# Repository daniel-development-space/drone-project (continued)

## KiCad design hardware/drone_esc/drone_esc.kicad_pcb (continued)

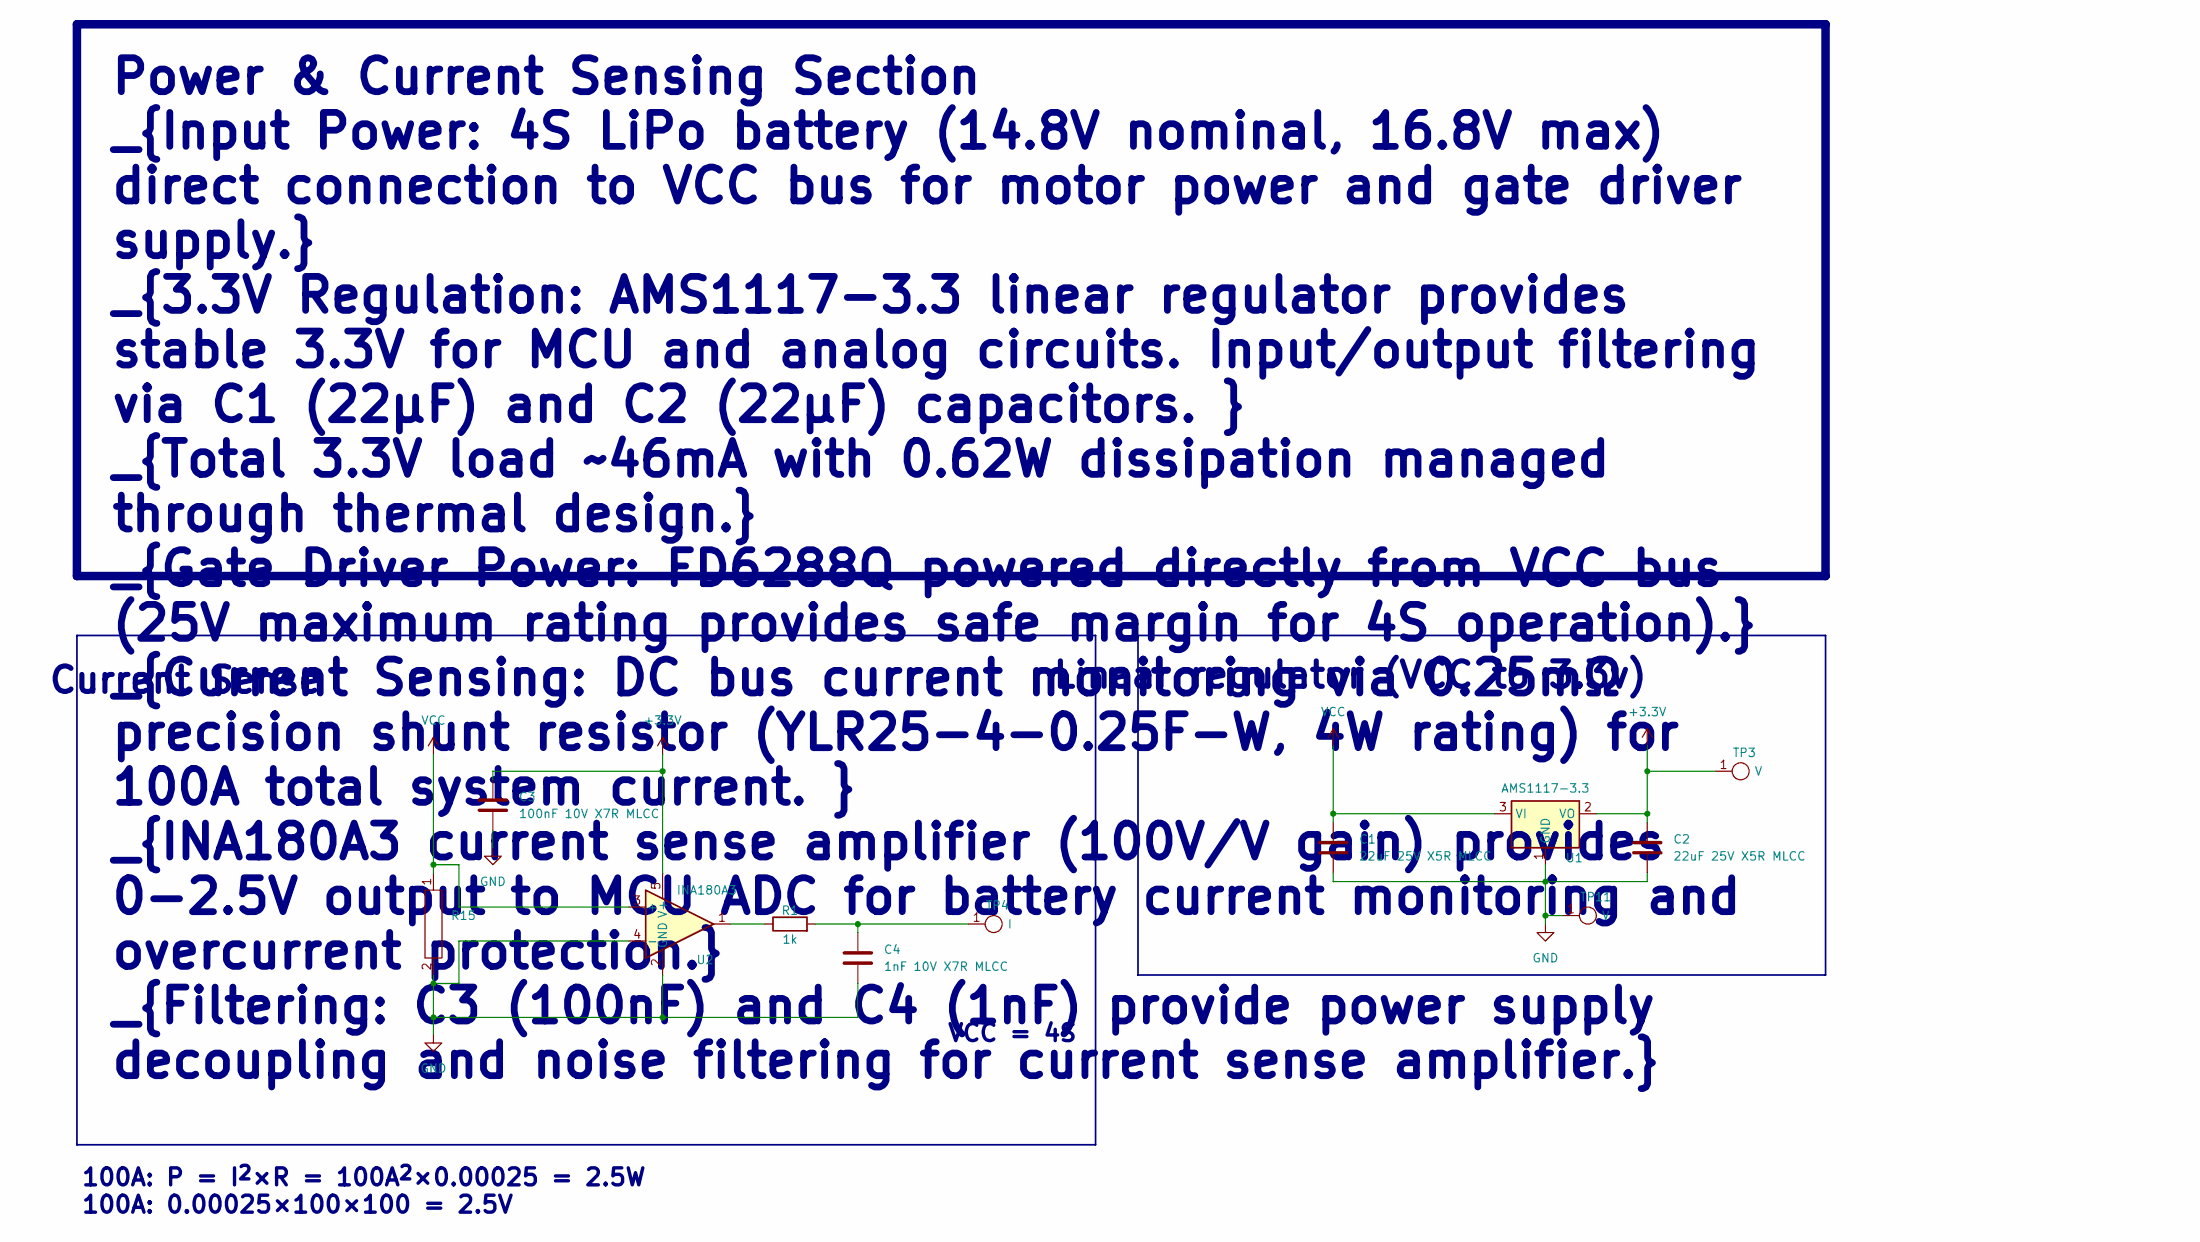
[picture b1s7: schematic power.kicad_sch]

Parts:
C1, C2: 22uF 25V X5R MLCC; C_0805_2012Metric; JLCPCB part C45783
C3: 100nF 10V X7R MLCC; C_0402_1005Metric; JLCPCB part C307331
C4: 1nF 10V X7R MLCC; C_0402_1005Metric; JLCPCB part C1523
R1: 1k; R_0402_1005Metric; JLCPCB part C11702
R15: YLR25-4-0.25F-W
TP3, TP11: V; Rectangle test point
TP4: I; Rectangle test point
U1: AMS1117-3.3; SOT-223-3_TabPin2; JLCPCB part C2688239
U2: INA180A3; SOT-23-5; JLCPCB part C122882

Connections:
+3.3V: C2.1, C3.1, TP3.1, U1.2 (VO), U2.5 (V+); also elsewhere on the board
GND: C1.2, C2.2, C3.2, C4.2, R15.2, TP11.1, U1.1 (GND), U2.2 (GND), U2.4 (-); also elsewhere on the board
unnamed: C4.1, R1.2, TP4.1
unnamed: R1.1, U2.1
VCC: C1.1, R15.1, U1.3 (VI), U2.3 (+); also elsewhere on the board

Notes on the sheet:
Linear regulator (VCC to 3.3v)
VCC = 4S
Current Sense
100A: P = I^{2}×R = 100A^{2}×0.00025 = 2.5W 100A: 0.00025×100×100 = 2.5V
Power & Current Sensing Section _{Input Power: 4S LiPo battery (14.8V nominal, 16.8V max) direct connection to VCC bus for motor power and gate driver supply.} _{3.3V Regulation: AMS1117-3.3 linear regulator provides stable 3.3V for MCU and analog circuits. Input/output filtering via C1 (22µF) and 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

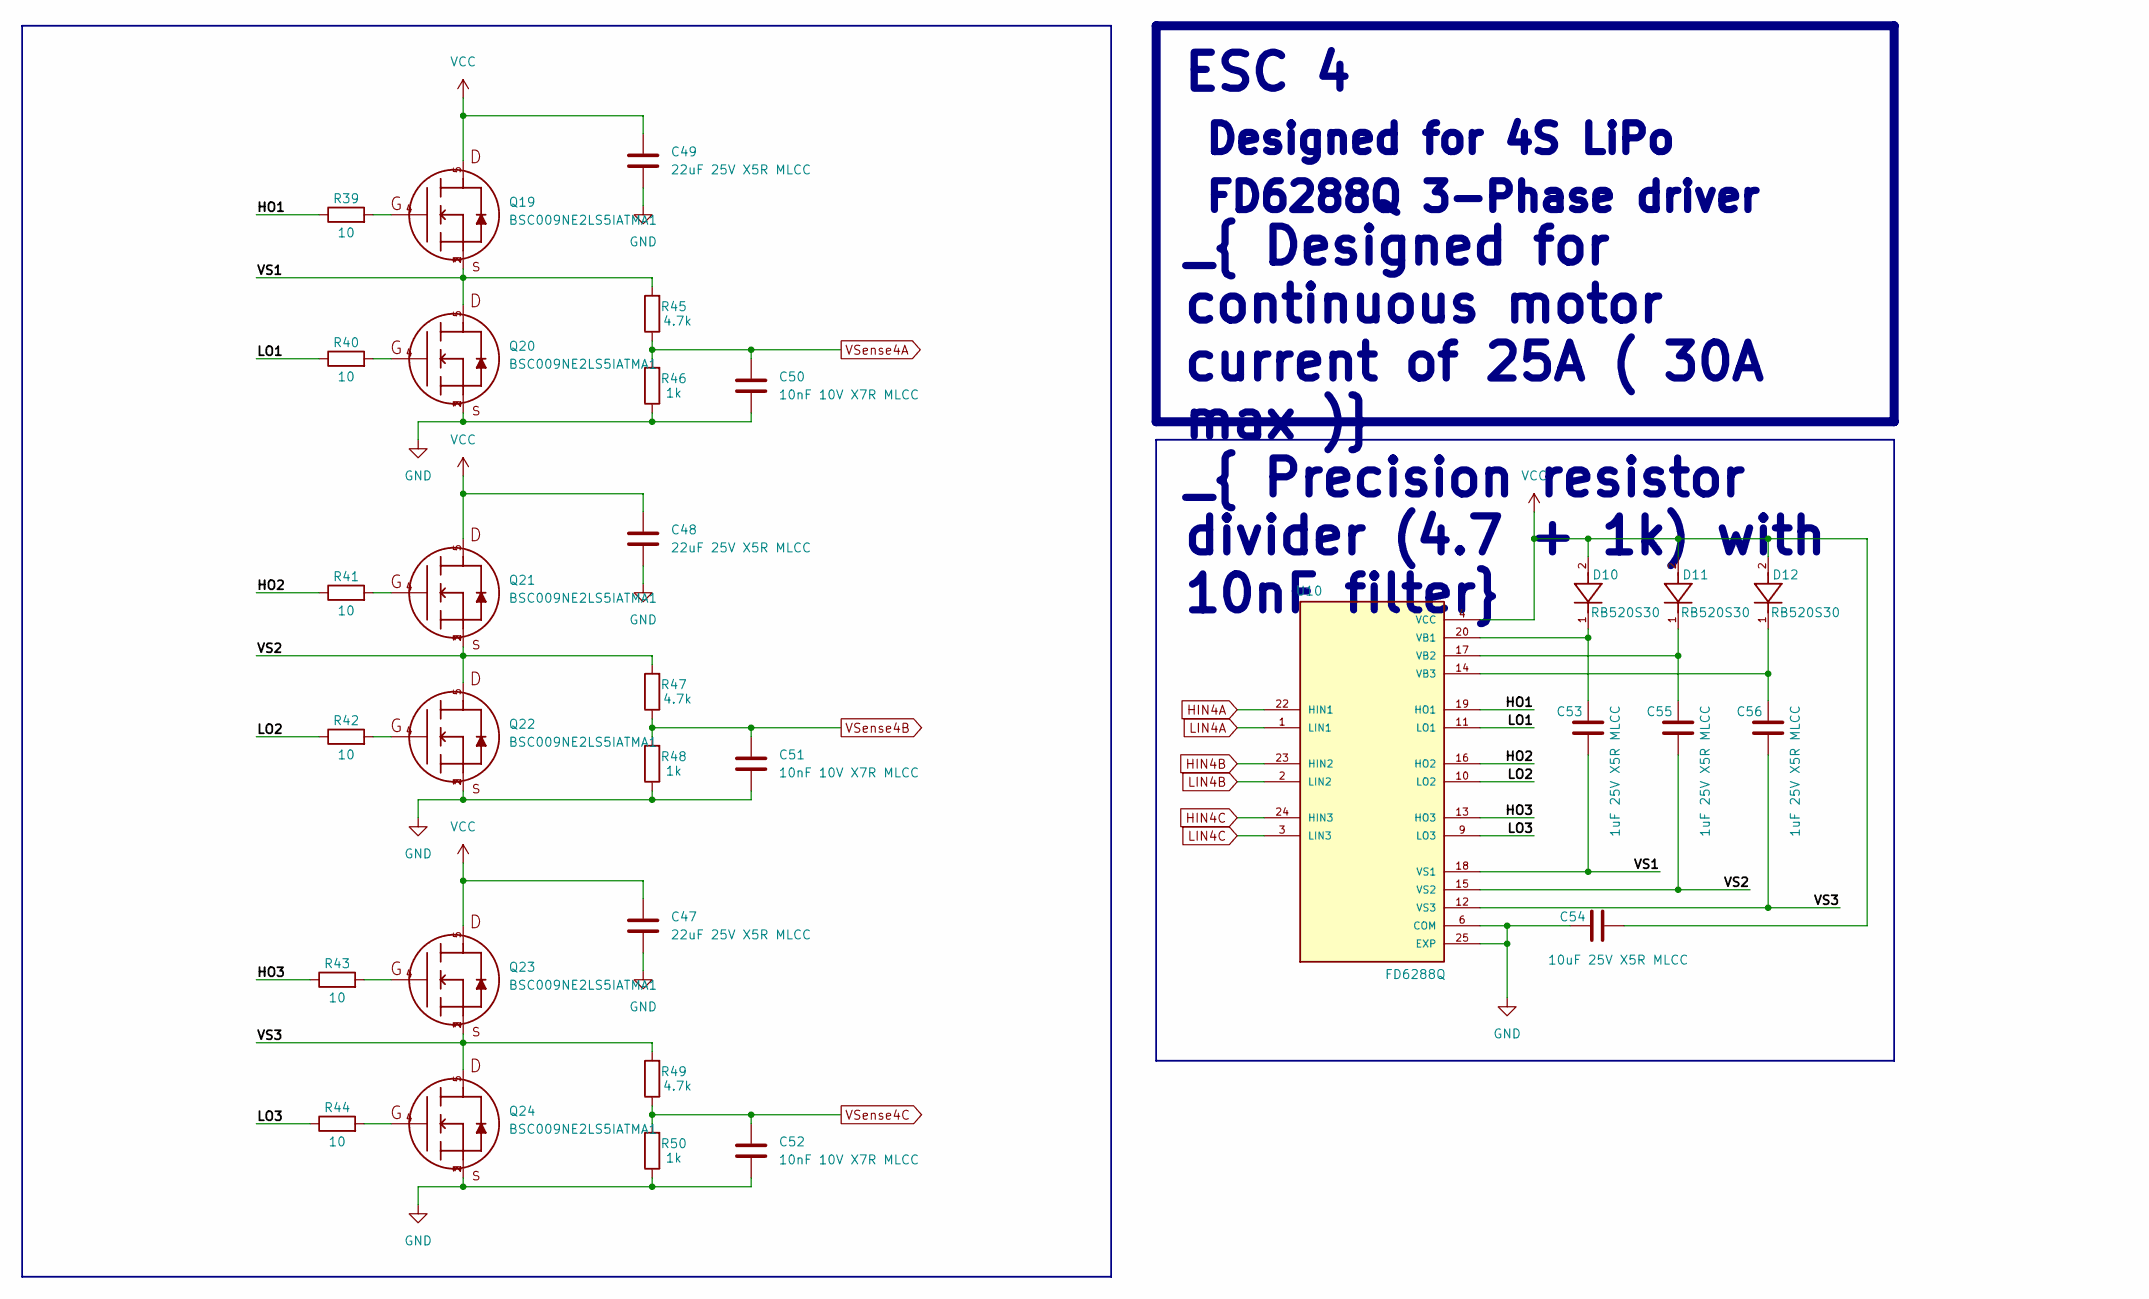
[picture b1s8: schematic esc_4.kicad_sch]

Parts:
C47, C48, C49: 22uF 25V X5R MLCC; C_0805_2012Metric; JLCPCB part C45783
C50, C51, C52: 10nF 10V X7R MLCC; C_0402_1005Metric; JLCPCB part C15195
C53, C55, C56: 1uF 25V X5R MLCC; C_0402_1005Metric; JLCPCB part C52923
C54: 10uF 25V X5R MLCC; C_0603_1608Metric; JLCPCB part C96446
D10, D11, D12: RB520S30; JLCPCB part C8522
Q19, Q20, Q21, Q22, Q23, Q24: BSC009NE2LS5IATMA1; BSC093N04LSGATMA1; JLCPCB part C122543
R39, R40, R41, R42, R43, R44: 10; R_0201_0603Metric; JLCPCB part C105889
R45, R47, R49: 4.7k; R_0402_1005Metric; JLCPCB part C25900
R46, R48, R50: 1k; R_0402_1005Metric; JLCPCB part C11702
U10: FD6288Q; JLCPCB part C328453

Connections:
/ESC4/HO1: R39.1, U10.19 (HO1)
/ESC4/HO2: R41.1, U10.16 (HO2)
/ESC4/HO3: R43.1, U10.13 (HO3)
/ESC4/LO1: R40.1, U10.11 (LO1)
/ESC4/LO2: R42.1, U10.10 (LO2)
/ESC4/LO3: R44.1, U10.9 (LO3)
/ESC4/VS1: C53.2, Q19.1, Q19.2, Q19.3, Q20.5, R45.2, U10.18 (VS1)
/ESC4/VS2: C55.2, Q21.1, Q21.2, Q21.3, Q22.5, R47.2, U10.15 (VS2)
/ESC4/VS3: C56.2, Q23.1, Q23.2, Q23.3, Q24.5, R49.2, U10.12 (VS3)
GND: C47.2, C48.2, C49.2, C50.2, C51.2, C52.2, C54.1, Q20.1, Q20.2, Q20.3, Q22.1, Q22.2, Q22.3, Q24.1, Q24.2, Q24.3, R46.1, R48.1, R50.1, U10.6 (COM), U10.25 (EXP); also elsewhere on the board
HIN4A: U10.22 (HIN1); also elsewhere on the board
HIN4B: U10.23 (HIN2); also elsewhere on the board
HIN4C: U10.24 (HIN3); also elsewhere on the board
LIN4A: U10.1 (LIN1); also elsewhere on the board
LIN4B: U10.2 (LIN2); also elsewhere on the board
LIN4C: U10.3 (LIN3); also elsewhere on the board
unnamed: Q19.4, R39.2
unnamed: Q20.4, R40.2
unnamed: Q21.4, R41.2
unnamed: Q22.4, R42.2
unnamed: Q23.4, R43.2
unnamed: Q24.4, R44.2
unnamed: C53.1, D10.1, U10.20 (VB1)
unnamed: C55.1, D11.1, U10.17 (VB2)
unnamed: C56.1, D12.1, U10.14 (VB3)
VCC: C47.1, C48.1, C49.1, C54.2, D10.2, D11.2, D12.2, Q19.5, Q21.5, Q23.5, U10.4 (VCC); also elsewhere on the board
VSense4A: C50.1, R45.1, R46.2; also elsewhere on the board
VSense4B: C51.1, R47.1, R48.2; also elsewhere on the board
VSense4C: C52.1, R49.1, R50.2; also elsewhere on the board

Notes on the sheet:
ESC 4 _{ Designed for 4S LiPo} _{ FD6288Q 3-Phase driver} _{ Designed for continuous motor current of 25A ( 30A max )} _{ Precision resistor divider (4.7 + 1k) with 10nF filter}

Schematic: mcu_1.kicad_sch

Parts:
C5: 4.7uF 10V X5R MLCC; C_0402_1005Metric; JLCPCB part C23733
C6: 100nF 10V X7R MLCC; C_0402_1005Metric; JLCPCB part C307331
C7: 100nF 16V X7R MLCC; C_0402_1005Metric; JLCPCB part C307331
TP1: 1.27 test pad
TP2: DShot; Rectangle test point
U3: STM32G071GBUxN; QFN-28_4x4mm_P0.5mm

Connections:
+3.3V: C5.1, C6.1, TP1.1 (V), U3.3 (VDD); also elsewhere on the board
/MCU1/SWCLK: TP1.3 (SWCLK), U3.21 (PA14)
/MCU1/SWDIO: TP1.2 (SWDIO), U3.20 (PA13)
GND: C5.2, C6.2, C7.1, TP1.4 (GND), U3.4 (VSS); also elsewhere on the board
HIN1A: U3.19 (PA10/PA12); also elsewhere on the board
HIN1B: U3.18 (PA9/PA11); also elsewhere on the board
HIN1C: U3.16 (PA8); also elsewhere on the board
LIN1A: U3.15 (PB15); also elsewhere on the board
LIN1B: U3.14 (PB0); also elsewhere on the board
LIN1C: U3.13 (PA7); also elsewhere on the board
unnamed: TP2.1, U3.28 (PB8)
unnamed: C7.2, U3.5 (PF2)
VSense1A: U3.6 (PA0); also elsewhere on the board
VSense1B: U3.7 (PA1); also elsewhere on the board
VSense1C: U3.8 (PA2); also elsewhere on the board

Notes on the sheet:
STM32G071GBU6
SWD Debugging
Microcontroller 1 _{Processor: 32-bit ARM Cortex-M0+ running at 64MHz for real-time 3-phase motor control and sensorless commutation algorithms.} _{Power: 3.3V regulated supply with C5 (1µF) and C6 (100nF) decoupling capacitors for stable operation.} _{Reset: PF2-NRST with C7 (100nF) filtering. Int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

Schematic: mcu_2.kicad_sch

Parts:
C18: 4.7uF 10V X5R MLCC; C_0402_1005Metric; JLCPCB part C23733
C19: 100nF 16V X7R MLCC; C_0402_1005Metric; JLCPCB part C307331
C20: 100nF 10V X7R MLCC; C_0402_1005Metric; JLCPCB part C307331
TP5: DShot; Rectangle test point
TP6: 1.27 test pad
U5: STM32G071GBU6; QFN-28_4x4mm_P0.5mm; JLCPCB part C529347

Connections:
+3.3V: C18.1, C20.1, TP6.1 (V), U5.3 (VDD); also elsewhere on the board
/MCU2/SWCLK: TP6.3 (SWCLK), U5.21 (PA14)
/MCU2/SWDIO: TP6.2 (SWDIO), U5.20 (PA13)
GND: C18.2, C19.1, C20.2, TP6.4 (GND), U5.4 (VSS); also elsewhere on the board
HIN2A: U5.19 (PA10/PA12); also elsewhere on the board
HIN2B: U5.18 (PA9/PA11); also elsewhere on the board
HIN2C: U5.16 (PA8); also elsewhere on the board
LIN2A: U5.15 (PB15); also elsewhere on the board
LIN2B: U5.14 (PB0); also elsewhere on the board
LIN2C: U5.13 (PA7); also elsewhere on the board
unnamed: TP5.1, U5.28 (PB8)
unnamed: C19.2, U5.5 (PF2)
VSense2A: U5.6 (PA0); also elsewhere on the board
VSense2B: U5.7 (PA1); also elsewhere on the board
VSense2C: U5.8 (PA2); also elsewhere on the board

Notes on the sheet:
SWD Debugging
STM32G071GBU6
Microcontroller 2 _{Processor: 32-bit ARM Cortex-M0+ running at 64MHz for real-time 3-phase motor control and sensorless commutation algorithms.} _{Power: 3.3V regulated supply with C5 (1µF) and C6 (100nF) decoupling capacitors for stable operation.} _{Reset: PF2-NRST with C7 (100nF) filtering. Int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

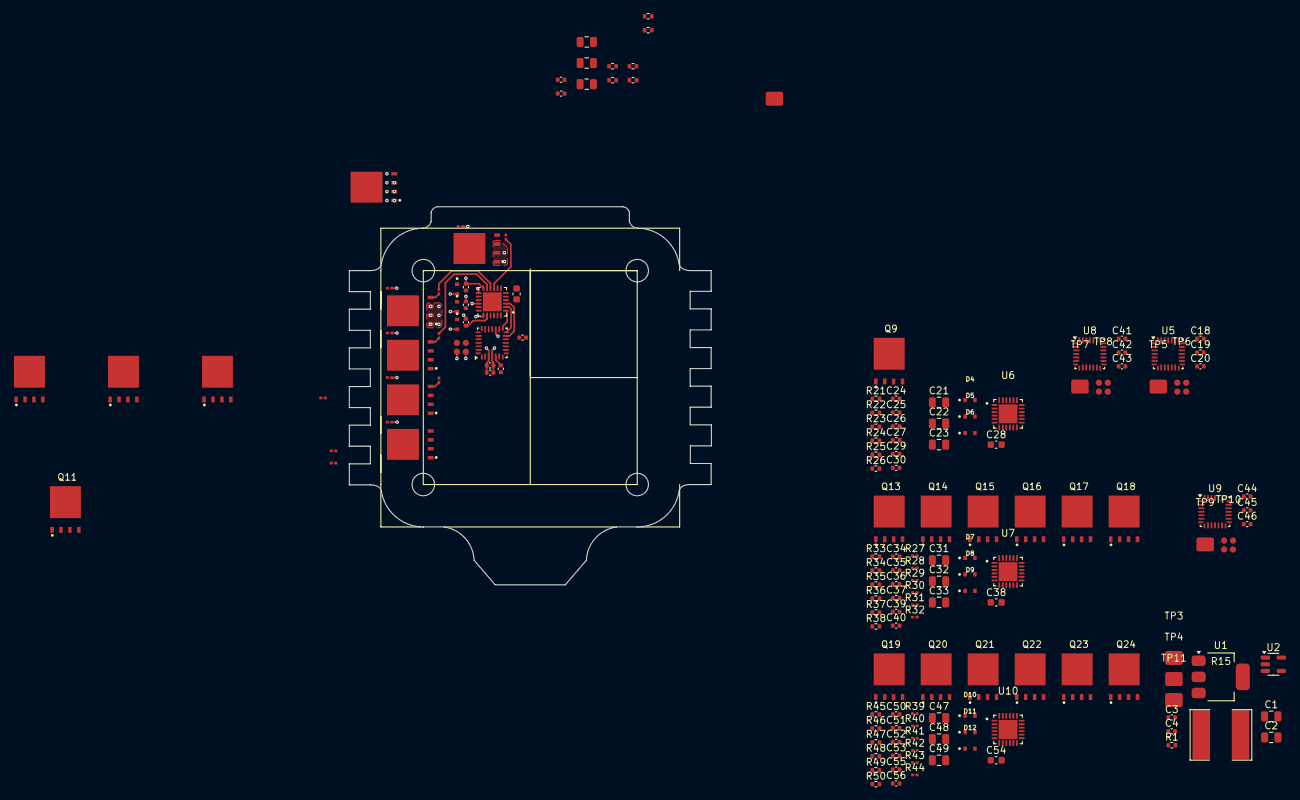
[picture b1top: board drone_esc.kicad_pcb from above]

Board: 6 copper layers, 51.6 x 53.9 mm, 167 parts (1 on the bottom side), 129 nets.

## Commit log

2025-08-04 Initial project setup with drone ESC design files
2025-08-04 created schematic hierarchy
2025-08-04 finished root schematics settings and drone overview
2025-08-04 Added footprint and symbol libraries
2025-08-04 created power schematics, assigned footprints and parts
2025-08-05 finished power section and one esc. need to finish the component assinment for jlcpcb and the rest of the esc
2025-08-05 finished 4 esc schematics need further refinment of the sheets
2025-08-05 finished the schematics and started to work on the PCB. need to find mcu model and finish the sheet description
2025-08-05 continued developing the pcb board
2025-08-06 finnished component placement
2025-08-07 need to connect the shunt resistor/ via stiching/ and finish power layer
2025-08-08 replaced some of the schematics
2025-08-09 changed some footprints and reconstracted the latout with better gate resistors clearence
